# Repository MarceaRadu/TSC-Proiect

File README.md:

# InkTime - Proiect 

InkTime este un prototip de ceas inteligent construit în jurul platformei SoC nRF52840. Dispozitivul dispune de un display color TFT, conectivitate Bluetooth Low Energy (BLE 5.0), senzor pentru detecția mișcării și utilizează un sistem de alimentare liniar, conceput special pentru a fi eficient în utilizarea cotidiană.

## 2. Tabel Componente (Bill Of Materials)

| Componentă / Rol | Format (Package) | Cod JLCPCB | Fișă Tehnică (Datasheet) |
|-----------|---------|-----------|-----------|
| **Microcontroler** (nRF52840-QIAA-R) | aQFN73 (7x7) | [C190794](https://jlcpcb.com/partdetail/Nordic_Semicon-NRF52840_QIAA_R/C190794) | [Datasheet](https://docs.nordicsemi.com/) |
| **Încărcător Baterie** (BQ25120YBGR) | DSBGA-9 | [C1682423](https://jlcpcb.com/partdetail/TexasInstruments-BQ25180YBGR/C3682423) | [Datasheet](https://www.ti.com/lit/ds/symlink/bq25180.pdf) |
| **Fuel Gauge** (MAX17048G+T10) | DFN-8 (2x2) | [C2682616](https://jlcpcb.com/partdetail/AnalogDevices-MAX17048G_T10/C2682616) | [Datasheet](https://www.analog.com/media/en/technical-documentation/data-sheets/MAX17048-MAX17049.pdf) |
| **Regulator Buck-Boost** (RT6160AWSC) | WLCSP-15 | [C7065276](https://jlcpcb.com/partdetail/Richtek_Tech-RT6160AWSC/C7065276) | [Datasheet](https://www.richtek.com/assets/product_file/RT6160A/DS6160A-05.pdf) |
| **Accelerometru** (BMA421) | LGA-12 (2x2) | [C5242966](https://jlcpcb.com/partdetail/Bosch_Sensortec-BMA421/C5242966) | [Datasheet](https://www.bosch-sensortec.com/media/boschsensortec/downloads/datasheets/bst-bma421-ds004.pdf) |
| **Driver Haptic** (DRV2605LDGSR) | VSSOP-10 | [C527464](https://jlcpcb.com/partdetail/TexasInstruments-DRV2605LDGSR/C527464) | [Datasheet](https://www.ti.com/lit/ds/symlink/drv2605l.pdf) |
| **Antenă BLE** (2450AT18B100E) | SMD 3216 | [C5179427](https://jlcpcb.com/partdetail/Johanson_Technology-2450AT18B100E/C5179427) | [Datasheet](https://www.johansontechnology.com/datasheets/2450AT18B100/2450AT18B100.pdf) |
| **Conector FPC** (Molex 503480-2400) | 24-pin 0.5mm FPC | [C2857168](https://jlcpcb.com/partdetail/Molex-5034802400/C2857160) | [Datasheet](https://www.molex.com/en-us/products/part-detail/5034802400) |
| **Butoane** (EVP-AKB31A) | SMD tactil | [C2845028](https://jlcpcb.com/partdetail/Panasonic-EVP_AKE31A/C2845028) | [Datasheet](https://industrial.panasonic.com/cdbs/www-data/pdf/ATV0000/ATV0000CE3.pdf) |
| **Mufă USB-C** (KH-TYPE-C-16P) | 16-pin SMD | [C2765186](https://jlcpcb.com/partdetail/Kinghelm-KH_TYPE_C_16P/C2765186) | [Datasheet](https://datasheet.lcsc.com/lcsc/2012121836_Kinghelm-KH-TYPE-C-16P_C2765186.pdf) |
| **Protecție ESD USB** (USBLC6-2SC6Y) | SOT-23-6 | [C7519](https://jlcpcb.com/partdetail/Stmicroelectronics-USBLC6_2SC6Y/C7519) | [Datasheet](https://www.st.com/resource/en/datasheet/usblc6-2.pdf) |
| **Tranzistor PFET** (Si2301CDS) | SOT-23 | [C10487](https://jlcpcb.com/partdetail/Changjiang_Electronics_Tech_CJ-SI2301CDS/C10487) | [Datasheet](https://www.vishay.com/docs/68749/si2301cds.pdf) |
| **Motor Vibrații** (LCM102733605F) | Fire atașate | [C7528006](https://jlcpcb.com/partdetail/7528806-LCM1027B3605F/C7528806) | [Datasheet](https://datasheet.lcsc.com/lcsc/2310131633_LCM-LCM1027B3605F_C7528806.pdf) |

**Componente Pasive & Periferice:**
* Interfață Programare: Header Tag-Connect 6-pin (TC2030-IDC)
* Cristale Oscilatoare: 32 MHz (2016) și 32.768 kHz (3215)
* Module externe: Display E-Paper / TFT 1.54 inch (FPC 24-pini), Acumulator LiPo 250 mAh
* Inductoare: 0.47uH (2012), 10uH (0402)
* Rezistențe (0201): 2x 10k, 2x 5.1k
* Condensatoare: 4x 12pF (0201), 5x 100nF (0201), 5x 4.7uF (0402), 2x 22uF (0402), 12x 1uF (0402)

## 3. Funcționalitatea Modulelor Hardware

**Unitatea de Procesare și Conectivitatea**
Creierul întregului sistem este cipul nRF52840 (la 64 MHz). Acesta execută logica aplicației și susține comunicarea wireless prin stiva BLE 5.0, permițând legătura cu smartphone-ul pentru sincronizarea timpului și preluarea notificărilor.

**Magistrale și Interfețe**
- **SPI (Doar transmisie):** Alocată exclusiv pentru display-ul TFT. Oferă o lățime de bandă mare, vitală pentru un framerate ridicat și tranziții fluide pe un ecran color.
- **I2C (400 kHz):** Prin intermediul acestei magistrale comunică senzorul inerțial (IMU) LSM6DS3TR-C. Folosirea I2C economisește pini valoroși și ușurează citirea datelor de accelerație.
- **PWM:** Comandă un tranzistor de tip N-MOSFET. Acesta joacă rolul de comutator de putere pentru motorul haptic (shaker-ul BST-BMV080), făcând posibilă generarea unor vibrații cu intensitate variabilă.

**Managementul Energiei (Power System)**
Pentru acest dispozitiv am implementat o arhitectură de alimentare liniară, punând accent pe fiabilitate și simplitate. Modulul BQ24040 primește 5V de la mufa USB-C și încarcă în condiții de siguranță bateria Li-Po de 250mAh (la un curent de 100mA). Mai departe, tensiunea variabilă a bateriei (3.0V - 4.2V) este coborâtă și stabilizată strict la 3.3V cu ajutorul unui regulator LDO (AP2112K). Acest LDO alimentează toată placa și a fost integrat datorită costului scăzut și a lipsei zgomotului electric la curenți mai mici de 600mA.

**Analiza Consumului de Energie**
Ecranele TFT, spre deosebire de cele e-paper, au nevoie de iluminare (backlight) continuă pentru a fi lizibile.
- *Consum în sarcină (Activ):* Aprox. 25 mA (TFT aprins la o luminozitate medie + procesorul activ).
- *Consum în repaus (Stand-by):* Aprox. 0.8 mA (Ecranul este oprit, MCU intră în modul sleep, funcția de BLE advertising este activă, iar IMU-ul așteaptă o mișcare pentru a trezi ceasul).
- *Estimare Autonomie:* Presupunând un scenariu zilnic cu 25 de treziri ale ecranului (a câte 5 secunde) și notificări haptice ocazionale, consumul se ponderează la o medie de 1.1 mA/h. În aceste condiții, acumulatorul de 250mAh asigură o durată de viață teoretică de 8 până la 9 zile de funcționare continuă.

## 4. Maparea Pinilor pentru nRF52840

Pinii au fost distribuiți având ca scop principal optimizarea traseelor de cupru pe placă (routing) și izolarea semnalelor rapide.

| Pin nRF | Periferic | Justificare / Rol Tehnic |
|---|---|---|
| **P0.29** | TFT SCK | Semnal de ceas rapid. Rutat special pe marginea PCB-ului către pamblica ecranului. |
| **P0.31** | TFT MOSI | Pin de date SPI. Tratat în paralel cu SCK pentru a evita degradarea semnalului grafic. |
| **P0.02** | TFT CS | Chip Select (activează display-ul pe magistrală). |
| **P0.26** | TFT DC | Data/Command. Necesar în mod obligatoriu pentru interpretarea comenzilor de către driverul ST7789. |
| **P0.27** | I2C SCL | Semnalul de clock pentru I2C, utilizat exclusiv de IMU. |
| **P0.28** | I2C SDA | Date I2C. Grupate special la distanță de liniile SPI pentru a elimina posibilele interferențe (crosstalk). |
| **P1.11** | Shaker PWM | Portul 1 a fost alocat pentru comenzi mecanice și de forță. Controlează grila tranzistorului de pe motoraș. |
| **P1.04** | Buton 1 (Sus) | GPIO setat ca intrare cu rezistență de pull-up internă. Folosit și pentru a trezi sistemul din hibernare. |
| **P1.05** | Buton 2 (OK) | Intrare digitală. Toți pinii butoanelor sunt adiacenți pentru a face rutarea pe margine extrem de scurtă. |
| **P1.06** | Buton 3 (Jos) | Intrare digitală pentru navigarea interfeței grafice. |
| **VBUS** | 5V USB | Pin hardware nativ al procesorului, capabil să citească prezența curentului de la încărcător. |
| **SWDIO** | Programare | Pin de date folosit la prima "flash-uire" a codului prin SWD / J-Link. |
| **SWDCLK**| Programare | Semnalul de ceas pentru protocolul de depanare SWD. |

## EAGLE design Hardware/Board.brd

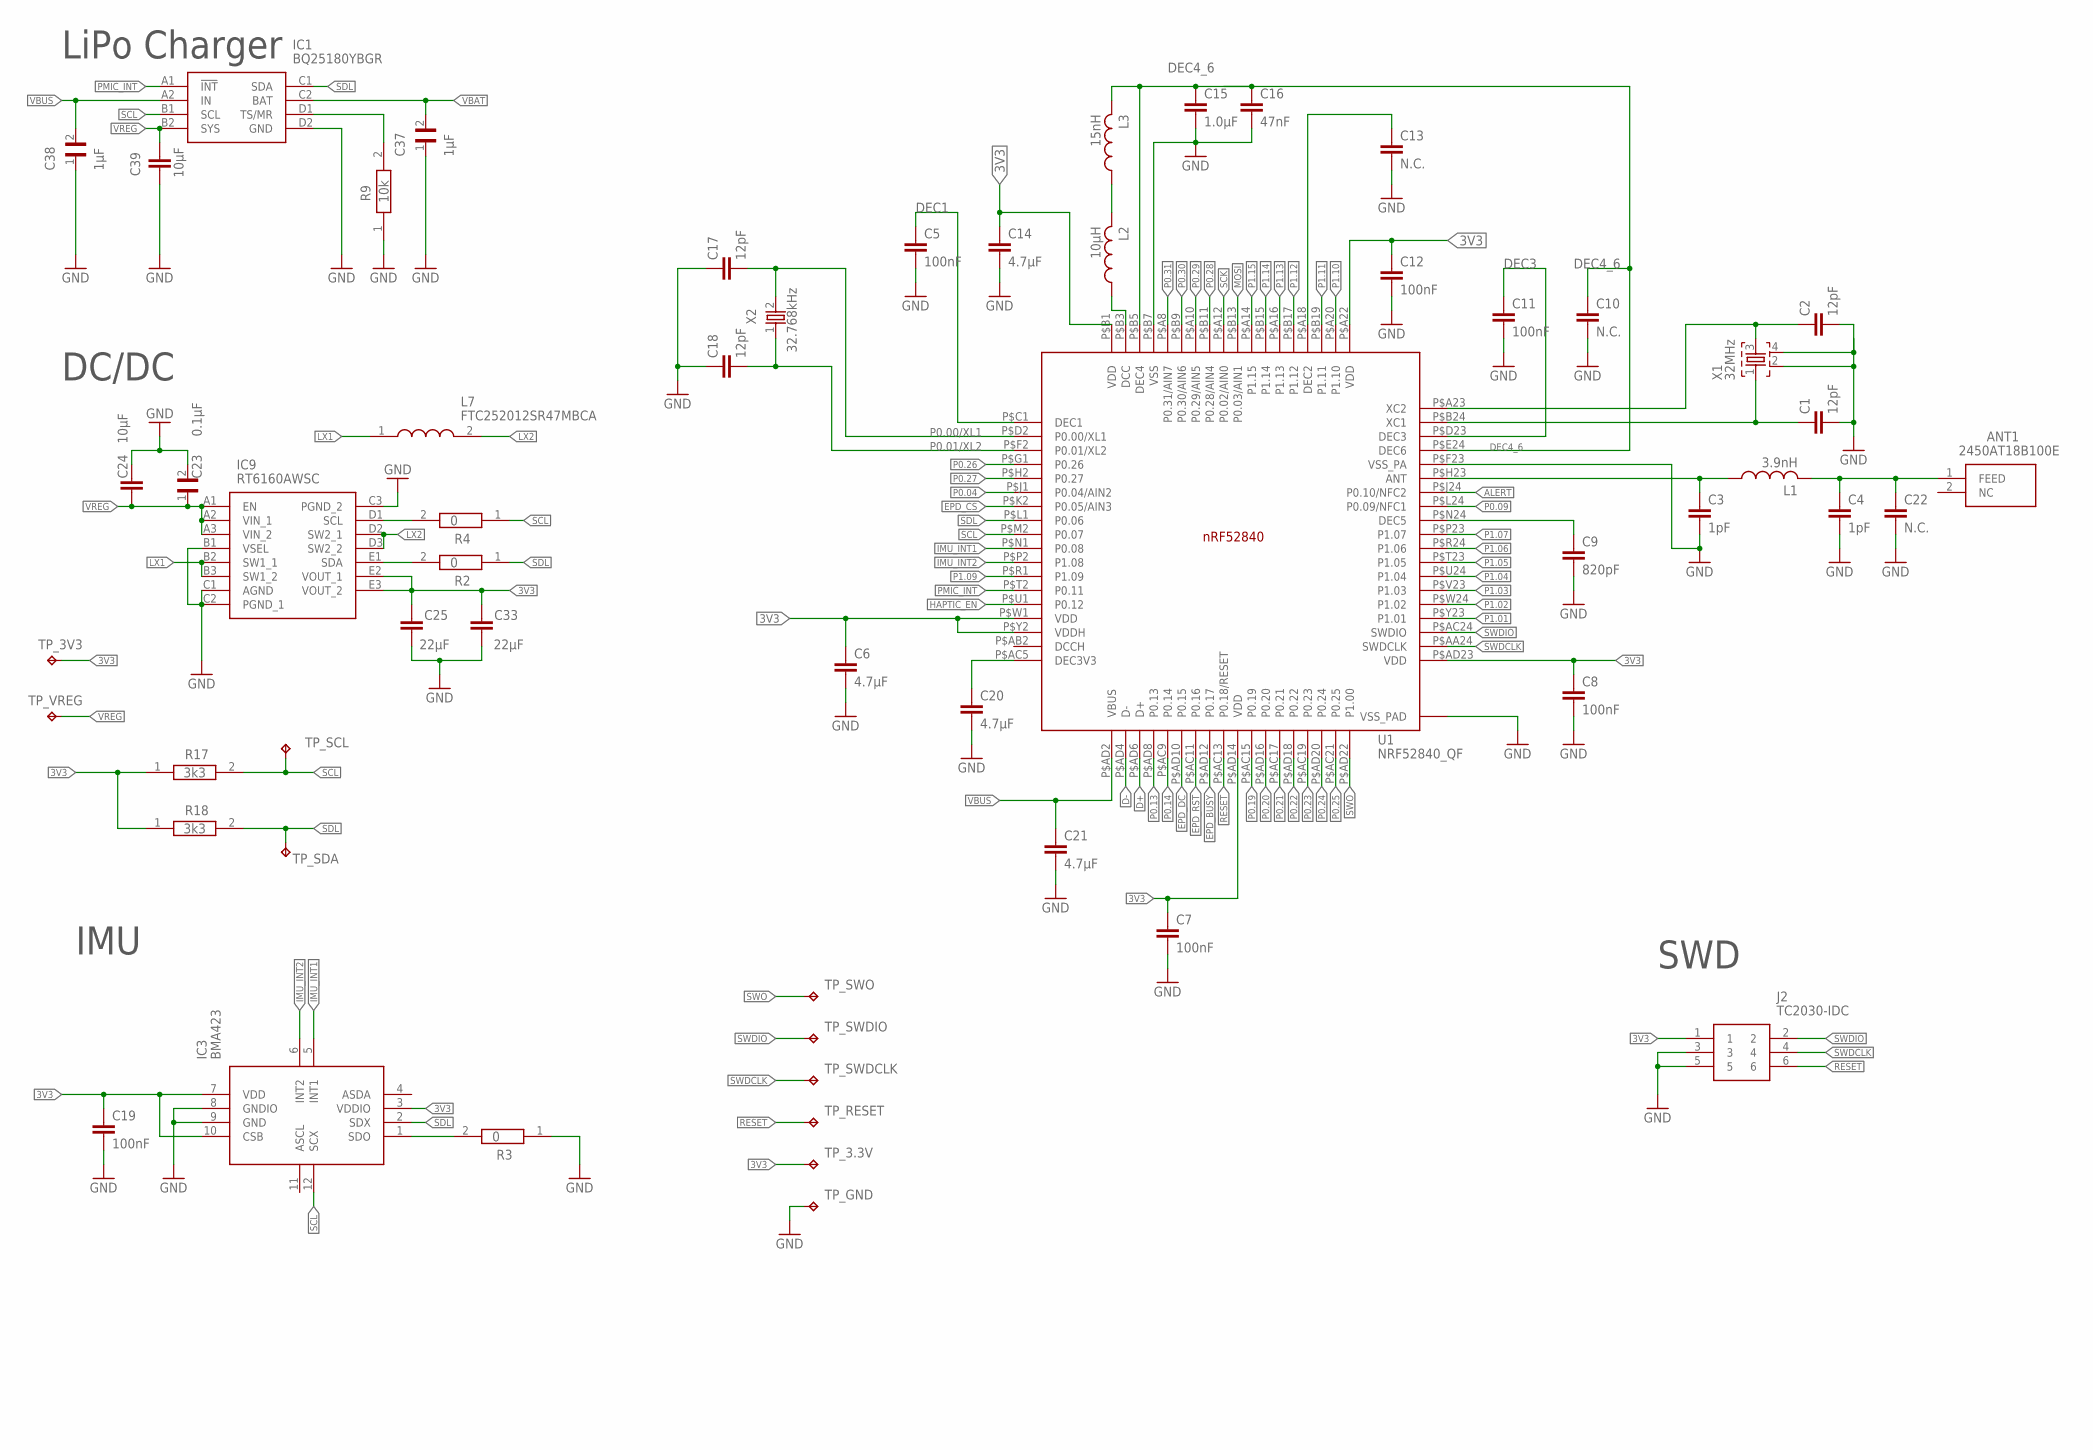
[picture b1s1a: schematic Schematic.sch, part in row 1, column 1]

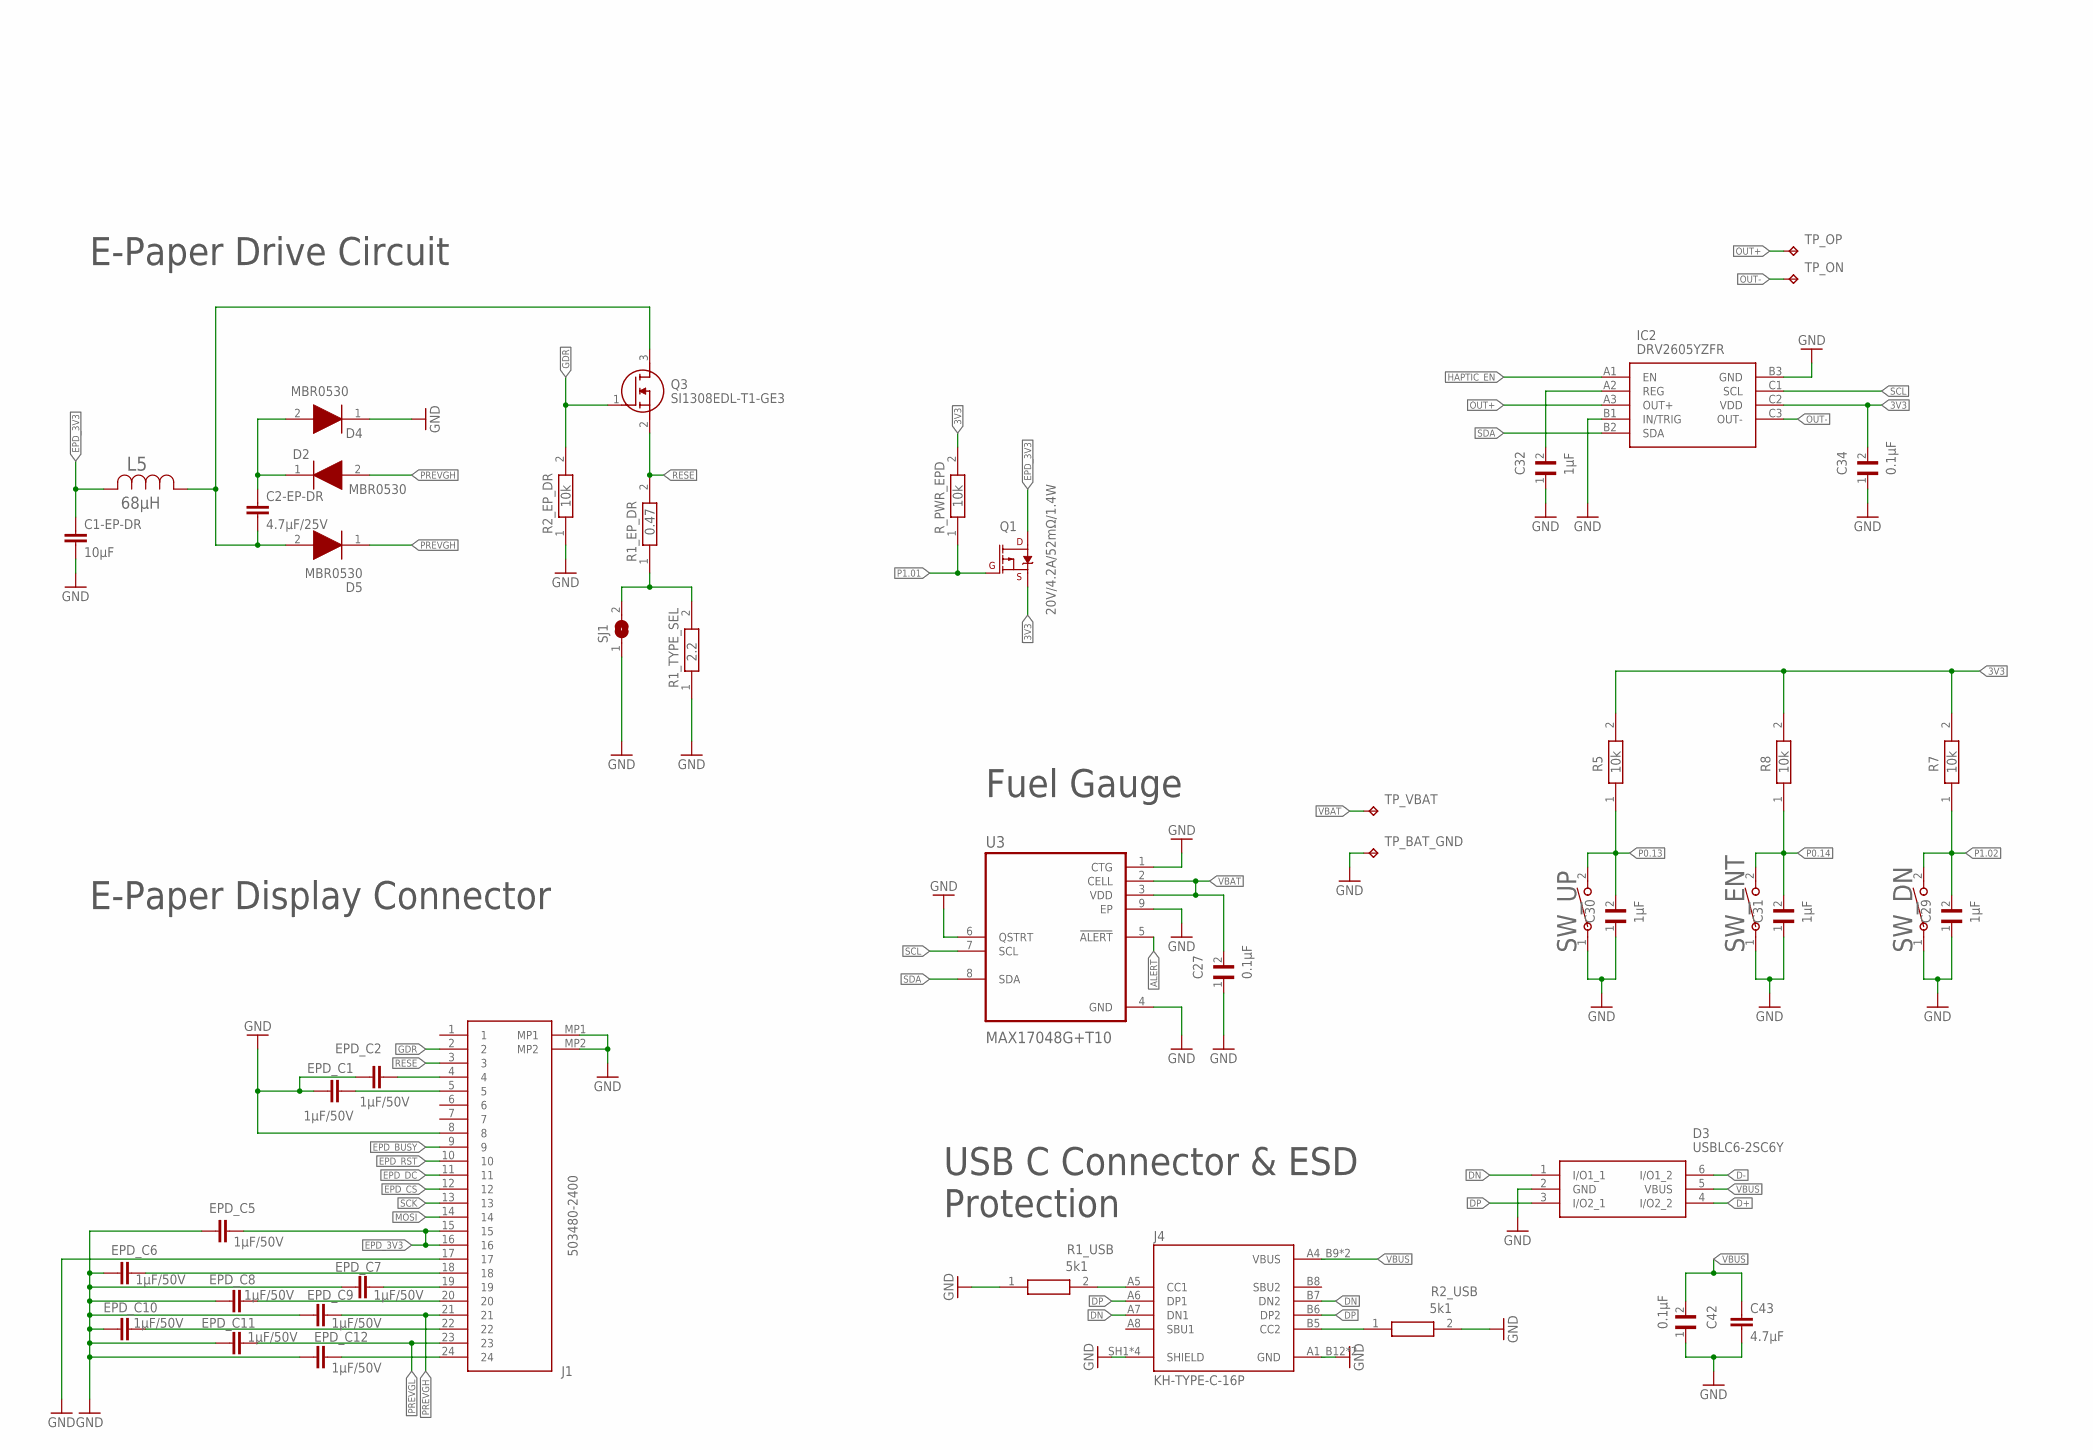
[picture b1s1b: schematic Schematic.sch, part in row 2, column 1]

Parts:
ANT1: 2450AT18B100E; 2450AT18B100E_ANTC3216X140N
C1, C2, C17, C18: 12pF; NORDIC_NRF_3_RESC0201_L
C1-EP-DR, C24, C39: 10μF; ESP32_C6_LIBRARY_1_ESP32_WROVER_EAGLE-LTSPICE_C0402
C2-EP-DR: 4.7μF/25V; ESP32_C6_LIBRARY_1_ESP32_WROVER_EAGLE-LTSPICE_C0402
C3, C4: 1pF; NORDIC_NRF_3_RESC0201_L
C5, C7, C8, C11, C12, C19: 100nF; NORDIC_NRF_3_RESC0201_L
C6, C14, C20, C21: 4.7μF; ESP32_C6_LIBRARY_1_ESP32_WROVER_EAGLE-LTSPICE_C0402
C9: 820pF; NORDIC_NRF_3_RESC0201_L
C10, C13, C22: N.C.; NORDIC_NRF_3_RESC0201_L
C15: 1.0μF; ESP32_C6_LIBRARY_1_ESP32_WROVER_EAGLE-LTSPICE_C0402
C16: 47nF; NORDIC_NRF_3_RESC0201_L
C23, C27, C34, C42: 0.1μF; GRM011R60J152KE01L_2_CAPC0201X13N
C25, C33: 22μF; ESP32_C6_LIBRARY_1_ESP32_WROVER_EAGLE-LTSPICE_C0402
C29, C30, C31, C32, C37, C38: 1μF; GRM011R60J152KE01L_2_CAPC0201X13N
C43: 4.7μF; PERFECT_0402_0402
D2, D4, D5: MBR0530; ESP32_C6_LIBRARY_5_SOD3716X135N
D3: USBLC6-2SC6Y; ESP32_C6_LIBRARY_3_SOT95P280X145-6N
EPD_C1, EPD_C2, EPD_C5, EPD_C6, EPD_C7, EPD_C8, EPD_C9, EPD_C10, EPD_C11, EPD_C12: 1μF/50V; PERFECT_0402_0402
IC1: BQ25180YBGR; BQ25180YBGR_BGA8C40P2X4_100X155X50
IC2: DRV2605YZFR; DRV2605YZFR_BGA9C50P3X3_144X144X62
IC3: BMA423; BMA423_BMA423
IC9: RT6160AWSC; RT6160AWSC_BGA15C40P3X5_140X230X60
J1: 503480-2400; 503480-2400_5034802400
J2: TC2030-IDC; TC2030-IDC_TC2030IDC
J4: KH-TYPE-C-16P; KH-TYPE-C-16P_KINGHELM_KH-TYPE-C-16P
L1: 3.9nH; NORDIC_NRF_2_RESC0402_L
L2: 10μH; NORDIC_NRF_2_RESC0402_L
L3: 15nH; NORDIC_NRF_2_RESC0402_L
L5: 68μH; ESP32_C6_LIBRARY_2_IND_4828-WE-TPC_WRE
L7: FTC252012SR47MBCA; MLP2016SR47MT0S1_INDC2016X100N
Q1: 20V/4.2A/52mΩ/1.4W; ESP32_C6_LIBRARY_4_ESP32_C6_LIBRARY_4_ESP32_C6_LIBRARY_4_ES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
Q3: SI1308EDL-T1-GE3; ESP32_C6_LIBRARY_4_ESP32_C6_LIBRARY_4_ESP32_C6_LIBRARY_4_ES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
R1_EP_DR: 0.47; ERA-1AEB3401C_0201
R1_TYPE_SEL: 2.2; ERA-1AEB3401C_0201
R1_USB, R2_USB: 5k1; ERA-1AEB3401C_0201
R2, R3, R4: 0; ERA-1AEB3401C_0201
R2_EP_DR, R5, R7, R8, R9: 10k; ERA-1AEB3401C_0201
R17, R18: 3k3; ERA-1AEB3401C_0201
R_PWR_EPD: 10k; ERA-1AEB3401C_0201
SJ1: ESP32_C6_LIBRARY_7_JUMPER_SJ
SW_DN: 2025-10-22_07-23-44_LIBRARY_EVP-AKE31ASW_EVP-AKE3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; 2025-10-22_07-23-44_LIBRARY_SW_EVP-AKE31A_PAN
SW_ENT: 2025-10-22_07-23-44_LIBRARY_EVP-AKE31ASW_EVP-AKE3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; 2025-10-22_07-23-44_LIBRARY_SW_EVP-AKE31A_PAN
SW_UP: 2025-10-22_07-23-44_LIBRARY_EVP-AKE31ASW_EVP-AKE3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; 2025-10-22_07-23-44_LIBRARY_SW_EVP-AKE31A_PAN
TP_3.3V, TP_3V3: HECTOR_WATCH_1_TPTP20R; HECTOR_WATCH_1_TP20R
TP_BAT_GND: HECTOR_WATCH_1_TPTP20R; HECTOR_WATCH_1_TP20R
TP_GND: HECTOR_WATCH_1_TPTP20R; HECTOR_WATCH_1_TP20R
TP_ON: HECTOR_WATCH_1_TPTP20R; HECTOR_WATCH_1_TP20R
TP_OP: HECTOR_WATCH_1_TPTP20R; HECTOR_WATCH_1_TP20R
TP_RESET: HECTOR_WATCH_1_TPTP20R; HECTOR_WATCH_1_TP20R
TP_SCL: HECTOR_WATCH_1_TPTP20R; HECTOR_WATCH_1_TP20R
TP_SDA: HECTOR_WATCH_1_TPTP20R; HECTOR_WATCH_1_TP20R
TP_SWDCLK: HECTOR_WATCH_1_TPTP20R; HECTOR_WATCH_1_TP20R
TP_SWDIO: HECTOR_WATCH_1_TPTP20R; HECTOR_WATCH_1_TP20R
TP_SWO: HECTOR_WATCH_1_TPTP20R; HECTOR_WATCH_1_TP20R
TP_VBAT: HECTOR_WATCH_1_TPTP20R; HECTOR_WATCH_1_TP20R
TP_VREG: HECTOR_WATCH_1_TPTP20R; HECTOR_WATCH_1_TP20R
U1: NRF52840_QF; NORDIC_NRF_4_AQFN50P700X700X85_HS-74N
U3: MAX17048G+T10; ESP32_C6_LIBRARY_SON50P200X200X80-9N
X1: 32MHz; NORDIC_NRF_BT-XTAL_2016_N
X2: 32.768kHz; NORDIC_NRF_1_XTAL_3215_N

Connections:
3V3: C6.1, C7.1, C8.1, C12.1, C14.1, C19.1, C33.1, C34.2, IC2.C2 (VDD), IC3.3 (VDDIO), IC3.7 (VDD), IC3.10 (CSB), IC9.E3 (VOUT_2), J2.1, Q1.2 (S), R5.2, R7.2, R8.2, R17.1, R18.1, R_PWR_EPD.2, TP_3.3V.TP, TP_3V3.TP, U1.P$A22 (VDD), U1.P$AD14 (VDD), U1.P$AD23 (VDD), U1.P$B1 (VDD), U1.P$W1 (VDD), U1.P$Y2 (VDDH)
ALERT: U1.P$J24 (P0.10/NFC2), U3.5 (!ALERT)
D+: D3.4 (I/O2_2), U1.P$AD6 (D+)
D-: D3.6 (I/O1_2), U1.P$AD4 (D-)
DEC1: C5.1, U1.P$C1 (DEC1)
DEC3: C11.1, U1.P$D23 (DEC3)
DEC4_6: C10.1, C15.1, C16.1, L3.2, U1.P$B5 (DEC4), U1.P$E24 (DEC6)
DN: D3.1 (I/O1_1), J4.A7 (DN1), J4.B7 (DN2)
DP: D3.3 (I/O2_1), J4.A6 (DP1), J4.B6 (DP2)
EPD_3V3: C1-EP-DR.1, EPD_C5.2, J1.15, J1.16, L5.2, Q1.3 (D)
EPD_BUSY: J1.9, U1.P$AD12 (P0.17)
EPD_CS: J1.12, U1.P$K2 (P0.05/AIN3)
EPD_DC: J1.11, U1.P$AD10 (P0.15)
EPD_RST: J1.10, U1.P$AC11 (P0.16)
GDR: J1.2, Q3.1 (G), R2_EP_DR.2
GND: C1.2, C1-EP-DR.2, C2.2, C3.2, C4.2, C5.2, C6.2, C7.2, C8.2, C9.2, C10.2, C11.2, C12.2, C13.2, C14.2, C15.2, C16.2, C17.1, C18.1, C19.2, C20.2, C21.2, C22.2, C23.2, C24.1, C25.2, C27.1, C29.1, C30.1, C31.1, C32.1, C33.2, C34.1, C37.1, C38.1, C39.2, C42.1, C43.2, D3.2 (GND), D4.1 (K), EPD_C1.1, EPD_C2.1, EPD_C5.1, EPD_C6.1, EPD_C7.1, EPD_C8.1, EPD_C9.1, EPD_C10.1, EPD_C11.1, EPD_C12.1, IC1.D2 (GND), IC2.B1 (IN/TRIG), IC2.B3 (GND), IC3.8 (GNDIO), IC3.9 (GND), IC9.B1 (VSEL), IC9.C1 (AGND), IC9.C2 (PGND_1), IC9.C3 (PGND_2), J1.8, J1.17, J1.MP1, J1.MP2, J2.3, J2.5, J4.A1_B12 (GND), J4.A12_B1 (GND), J4.SH1 (SHIELD), J4.SH2 (SHIELD), J4.SH3 (SHIELD), J4.SH4 (SHIELD), R1_TYPE_SEL.1, R1_USB.1, R2_EP_DR.1, R2_USB.2, R3.1, R9.1, SJ1.1, SW_DN.1, SW_ENT.1, SW_UP.1, TP_BAT_GND.TP, TP_GND.TP, U1.P$74 (VSS_PAD), U1.P$75 (VSS_PAD), U1.P$76 (VSS_PAD), U1.P$77 (VSS_PAD), U1.P$78 (VSS_PAD), U1.P$79 (VSS_PAD), U1.P$80 (VSS_PAD), U1.P$81 (VSS_PAD), U1.P$82 (VSS_PAD), U1.P$83 (VSS_PAD), U1.P$84 (VSS_PAD), U1.P$85 (VSS_PAD), U1.P$86 (VSS_PAD), U1.P$87 (VSS_PAD), U1.P$88 (VSS_PAD), U1.P$89 (VSS_PAD), U1.P$90 (VSS_PAD), U1.P$B7 (VSS), U1.P$F23 (VSS_PA), U3.1 (CTG), U3.4 (GND), U3.6 (QSTRT), U3.9 (EP), X1.2, X1.4
HAPTIC_EN: IC2.A1 (EN), U1.P$U1 (P0.12)
IMU_INT1: IC3.5 (INT1), U1.P$N1 (P0.08)
IMU_INT2: IC3.6 (INT2), U1.P$P2 (P1.08)
LX1: IC9.B2 (SW1_1), IC9.B3 (SW1_2), L7.1
LX2: IC9.D2 (SW2_1), IC9.D3 (SW2_2), L7.2
MOSI: J1.14, U1.P$B13 (P0.03/AIN1)
unnamed: L2.1, U1.P$B3 (DCC)
unnamed: L2.2, L3.1
unnamed: C13.1, U1.P$A18 (DEC2)
unnamed: C1.1, U1.P$B24 (XC1), X1.1
unnamed: C2.1, U1.P$A23 (XC2), X1.3
unnamed: C3.1, L1.1, U1.P$H23 (ANT)
unnamed: ANT1.1 (FEED), C4.1, C22.1, L1.2
unnamed: C9.1, U1.P$N24 (DEC5)
unnamed: C20.1, U1.P$AC5 (DEC3V3)
unnamed: IC9.D1 (SCL), R4.2
unnamed: IC9.E1 (SDA), R2.2
unnamed: IC1.D1 (TS/MR), R9.2
unnamed: C25.1, IC9.E2 (VOUT_1)
unnamed: IC3.1 (SDO), R3.2
unnamed: C2-EP-DR.2, D5.2 (A), L5.1, Q3.3 (D)
unnamed: C2-EP-DR.1, D2.1 (K), D4.2 (A)
unnamed: R1_EP_DR.1, R1_TYPE_SEL.2, SJ1.2
unnamed: EPD_C2.2, J1.4
unnamed: EPD_C1.2, J1.5
unnamed: EPD_C6.2, J1.18
unnamed: EPD_C7.2, J1.19
unnamed: EPD_C8.2, J1.20
unnamed: J4.A5 (CC1), R1_USB.2
unnamed: EPD_C10.2, J1.22
unnamed: J4.B5 (CC2), R2_USB.1
unnamed: EPD_C12.2, J1.24
unnamed: C32.2, IC2.A2 (REG)
OUT+: IC2.A3 (OUT+), TP_OP.TP
OUT-: IC2.C3 (OUT-), TP_ON.TP
P0.00/XL1: C17.2, U1.P$D2 (P0.00/XL1), X2.2
P0.01/XL2: C18.2, U1.P$F2 (P0.01/XL2), X2.1
P0.04: U1.P$J1 (P0.04/AIN2)
P0.09: U1.P$L24 (P0.09/NFC1)
P0.13: C30.2, R5.1, SW_UP.2, U1.P$AD8 (P0.13)
P0.14: C31.2, R8.1, SW_ENT.2, U1.P$AC9 (P0.14)
P0.19: U1.P$AC15 (P0.19)
P0.20: U1.P$AD16 (P0.20)
P0.21: U1.P$AC17 (P0.21)
P0.22: U1.P$AD18 (P0.22)
P0.23: U1.P$AC19 (P0.23)
P0.24: U1.P$AD20 (P0.24)
P0.25: U1.P$AC21 (P0.25)
P0.26: U1.P$G1 (P0.26)
P0.27: U1.P$H2 (P0.27)
P0.28: U1.P$B11 (P0.28/AIN4)
P0.29: U1.P$A10 (P0.29/AIN5)
P0.30: U1.P$B9 (P0.30/AIN6)
P0.31: U1.P$A8 (P0.31/AIN7)
P1.01: Q1.1 (G), R_PWR_EPD.1, U1.P$Y23 (P1.01)
P1.02: C29.2, R7.1, SW_DN.2, U1.P$W24 (P1.02)
P1.03: U1.P$V23 (P1.03)
P1.04: U1.P$U24 (P1.04)
P1.05: U1.P$T23 (P1.05)
P1.06: U1.P$R24 (P1.06)
P1.07: U1.P$P23 (P1.07)
P1.09: U1.P$R1 (P1.09)
P1.10: U1.P$A20 (P1.10)
P1.11: U1.P$B19 (P1.11)
P1.12: U1.P$B17 (P1.12)
P1.13: U1.P$A16 (P1.13)
P1.14: U1.P$B15 (P1.14)
P1.15: U1.P$A14 (P1.15)
PMIC_INT: IC1.A1 (!INT), U1.P$T2 (P0.11)
PREVGH: D2.2 (A), D5.1 (K), EPD_C9.2, J1.21
PREVGL: EPD_C11.2, J1.23
RESE: J1.3, Q3.2 (S), R1_EP_DR.2
RESET: J2.6, TP_RESET.TP, U1.P$AC13 (P0.18/RESET)
SCK: J1.13, U1.P$A12 (P0.02/AIN0)
SCL: IC1.B1 (SCL), IC2.C1 (SCL), IC3.12 (SCX), R4.1, R17.2, TP_SCL.TP, U1.P$M2 (P0.07), U3.7 (SCL)
SDA: IC2.B2 (SDA), U3.8 (SDA)
SDL: IC1.C1 (SDA), IC3.2 (SDX), R2.1, R18.2, TP_SDA.TP, U1.P$L1 (P0.06)
SWDCLK: J2.4, TP_SWDCLK.TP, U1.P$AA24 (SWDCLK)
SWDIO: J2.2, TP_SWDIO.TP, U1.P$AC24 (SWDIO)
SWO: TP_SWO.TP, U1.P$AD22 (P1.00)
VBAT: C27.2, C37.2, IC1.C2 (BAT), TP_VBAT.TP, U3.2 (CELL), U3.3 (VDD)
VBUS: C21.1, C38.2, C42.2, C43.1, D3.5 (VBUS), IC1.A2 (IN), J4.A4_B9 (VBUS), J4.A9_B4 (VBUS), U1.P$AD2 (VBUS)
VREG: C23.1, C24.2, C39.1, IC1.B2 (SYS), IC9.A1 (EN), IC9.A2 (VIN_1), IC9.A3 (VIN_2), TP_VREG.TP

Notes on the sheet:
SWD
LiPo Charger
DC/DC
IMU
E-Paper Drive Circuit
E-Paper Display Connector
Fuel Gauge
USB C Connector & ESD Protection

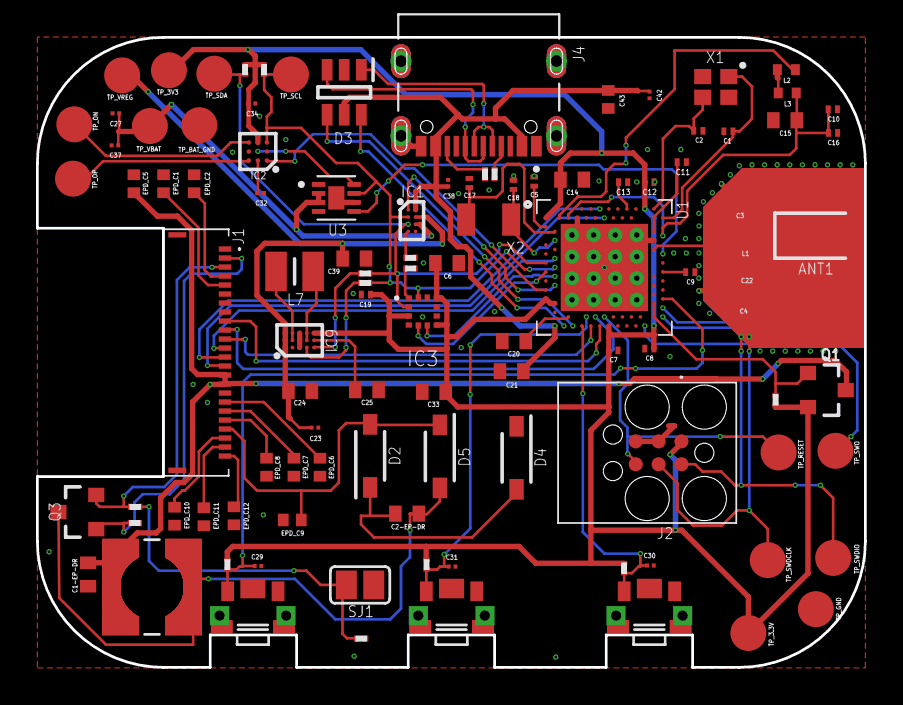
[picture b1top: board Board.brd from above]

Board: 2 copper layers, 46.0 x 35.0 mm, 105 parts (0 on the bottom side), 72 nets.

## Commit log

2026-04-20 Create a
2026-04-20 Rename Schematic.sch to Hardware/Schematic.sch
2026-04-20 Create LICENSE

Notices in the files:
parts and their libraries:
COPYRIGHT: Copyright (C) 2024 Ultra Librarian. All rights reserved.
COPYRIGHT: Copyright (C) 2025 Ultra Librarian. All rights reserved.
